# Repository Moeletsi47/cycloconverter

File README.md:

# Single-Phase Cycloconverter | ATmega328P

An embedded power-electronics project combining SCR switching, zero-crossing synchronisation, register-level C firmware, and a custom four-layer PCB designed in KiCad.

The intended input is **230 V AC RMS at 50 Hz**. The firmware runs an automatic sequence of frequency and voltage targets, then ramps down and disables gate firing.

## Operating sequence

The uploaded firmware uses a nominal **5 V/Hz** lookup table and the following sequence:

| Step | Frequency target | Nominal voltage target | Duration |
| --- | --- | --- | --- |
| Ramp up | 0 → 10 Hz | 0 → 50 V | 5 s |
| Hold | 10 Hz | 50 V | 2 s |
| Ramp up | 10 → 20 Hz | 50 → 100 V | 5 s |
| Hold | 20 Hz | 100 V | 2 s |
| Ramp up | 20 → 40 Hz | 100 → 200 V | 5 s |
| Hold | 40 Hz | 200 V | 2 s |
| Ramp down | 40 → 0 Hz | 200 → 0 V | 5 s |

After ramp-down, the controller remains in its stopped state until reset. The firmware reaches zero after 5 seconds of ramp-down and enters its final state at the next 500 ms update.

The hold-time comments in the source say 10 seconds, but the implemented thresholds are 2000 ms, giving **2-second holds**.

Voltage values are intended lookup-table targets, not measurements or closed-loop regulation. The switched output is non-sinusoidal; its RMS voltage and frequency spectrum require waveform verification, particularly at the 40 Hz setting.

## Firmware

The controller is an **ATmega328P running at 16 MHz**, programmed in embedded C using direct register access.

- **Zero-crossing interrupt:** PB0 / PCINT0 supplies the input timing reference.
- **Timer1:** Schedules the firing delay and gate-pulse duration with a prescaler of 64.
- **Gate pulses:** Approximately 300 µs, based on `PULSE_TICKS = 74`.
- **Timer2:** Generates a 1 ms timebase for the ramp and hold sequence.
- **Frequency control:** A phase accumulator selects the commanded output polarity at input half-cycle boundaries.
- **Voltage control:** `fire_table[]` selects a firing delay for each frequency setpoint.
- **Shutdown:** A zero-frequency setpoint prevents further gate firing.

The control sequence runs in interrupt service routines; the main loop remains idle.

## Pin mapping

| Signal | ATmega328P pin |
| --- | --- |
| Zero-crossing input | PB0 |
| T1 | PB1 |
| T2 | PB2 |
| T3 | PB3 |
| T4 | PB4 |
| N1 | PD4 |
| N2 | PD5 |
| N3 | PD6 |
| N4 | PD7 |

This firmware defines **eight gate outputs** in two groups. Confirm that the schematic and PCB revision match this mapping before using the firmware; the earlier four-SCR PCB arrangement must not be assumed to match it directly.

## Four-layer PCB design

The project also includes a **custom four-layer PCB designed in KiCad**, with attention to the separation of mains circuitry and low-voltage control electronics.

PCB design features include:

- Separate high-voltage power and low-voltage control regions.
- Isolation keepout regions around the optocoupler barrier.
- An internal ground pour confined to the low-voltage region.
- Wider copper tracks for the main SCR and load-current paths.
- Dedicated routing classes for power, mains sensing, and control signals.
- RC snubbers placed close to the associated switching devices.
- Input fuse and MOV provision.
- External power headers and terminal-block connections.

The design work covers schematic capture, footprint assignment, multilayer routing, and fabrication-output preparation. PCB layout completion does not by itself establish hardware validation or electrical-safety compliance.

## Development tools

| Tool | Purpose |
| --- | --- |
| Microchip Studio | AVR firmware development |
| Proteus | Circuit simulation and waveform inspection |
| KiCad | Schematic capture and four-layer PCB design |

## Current limitations and future improvements

- Output voltage is controlled through a fixed lookup table; the supplied firmware has no voltage-feedback loop.
- Input polarity is inferred by alternating a software flag at each accepted zero-crossing event.
- The supplied firmware has no current-zero detection or current-based interlock between converter groups.
- Planned improvements include current sensing, commutation interlocking, and measured calibration of the voltage targets.

## Safety

This project involves hazardous 230 V AC. Gate signals turning off do not force an SCR to stop conducting. Hardware testing requires appropriate protection, mains-rated measurement equipment, and verification of commutation behaviour, especially with inductive loads.

## Author

Jason Nkuna

Embedded systems, power electronics, and PCB design.

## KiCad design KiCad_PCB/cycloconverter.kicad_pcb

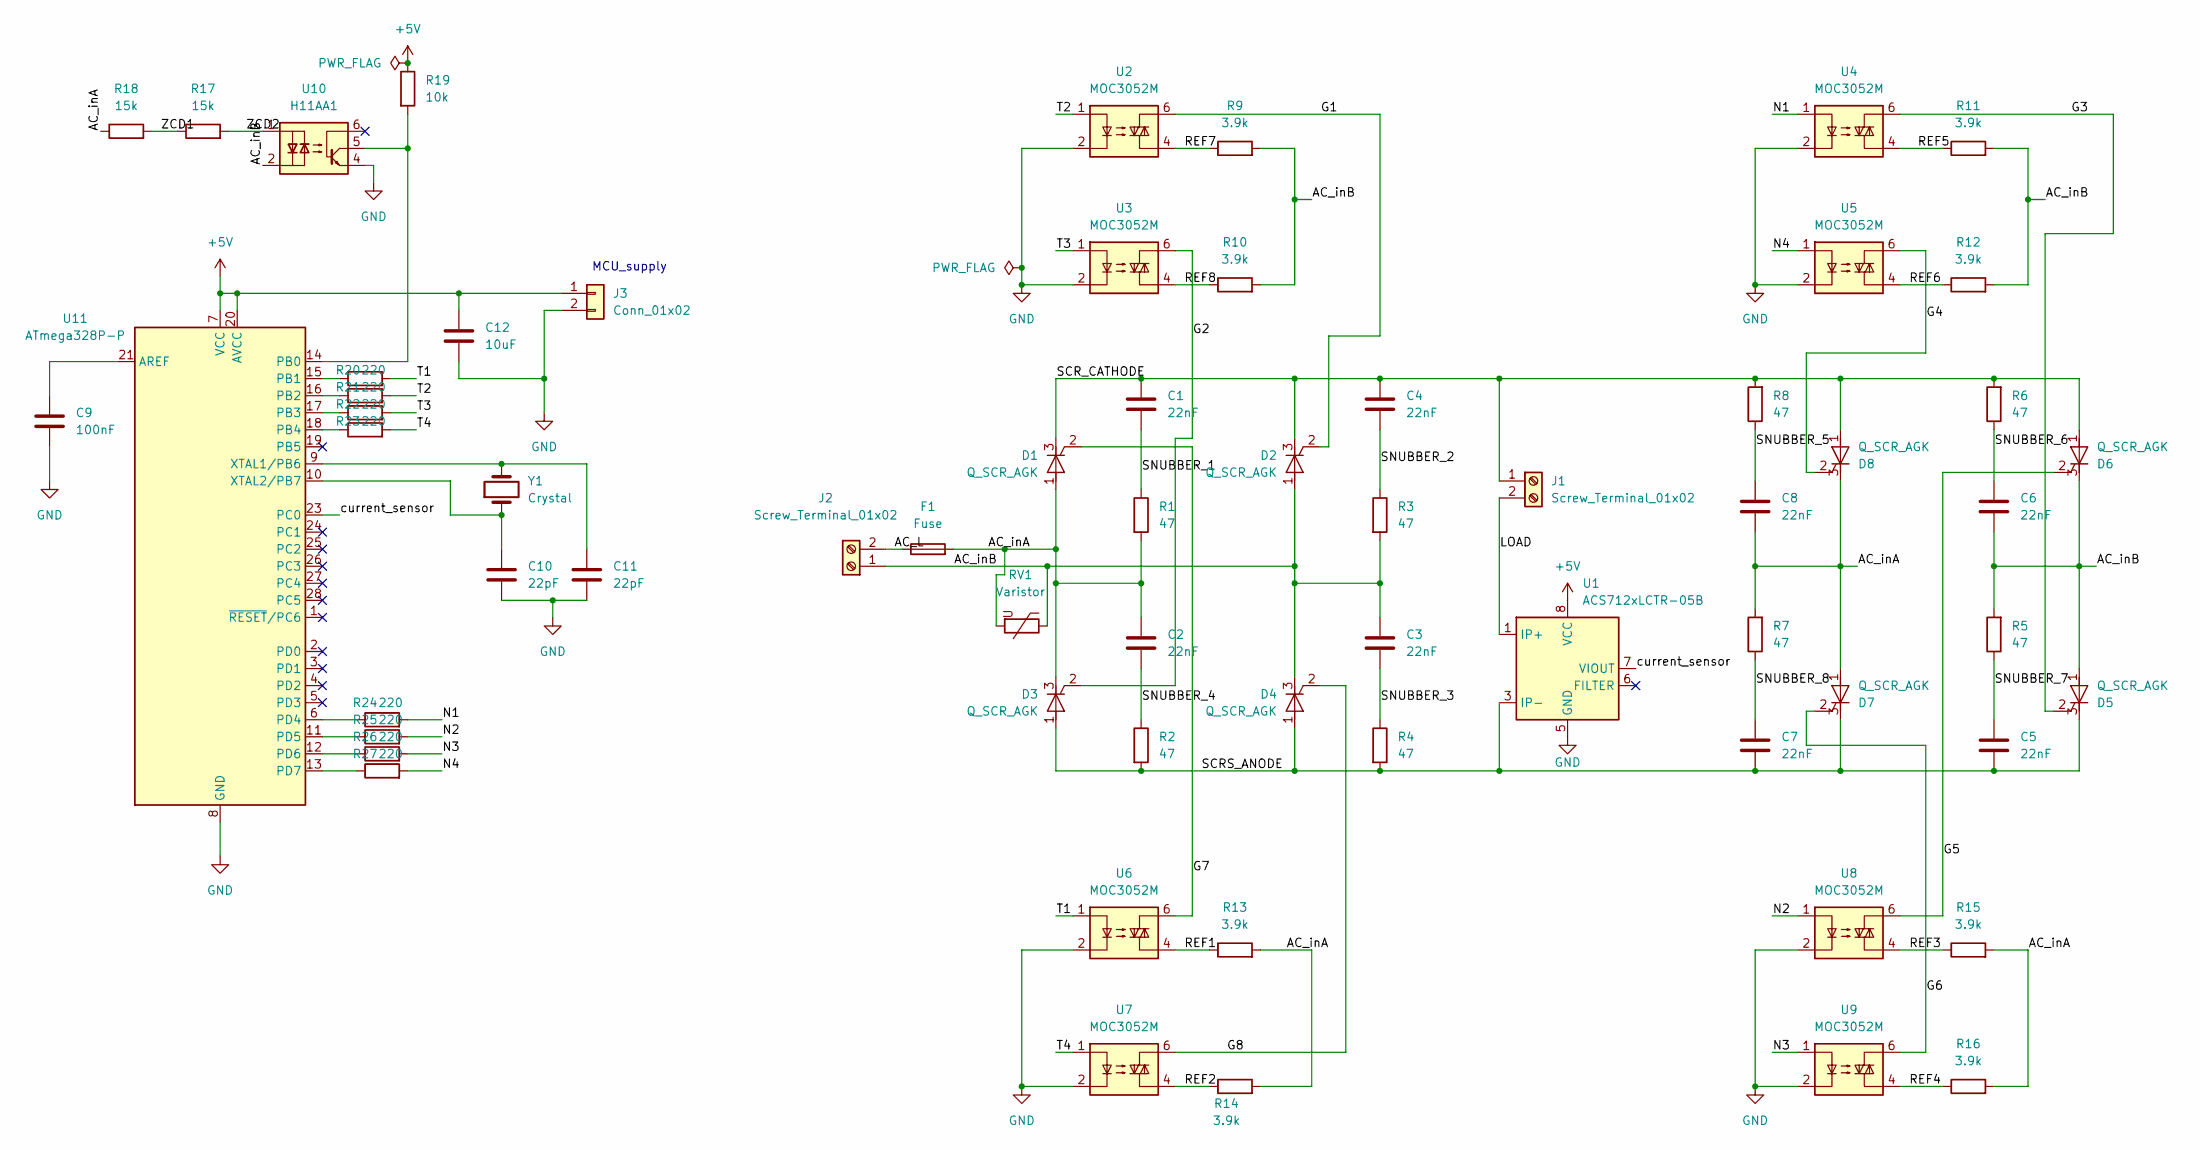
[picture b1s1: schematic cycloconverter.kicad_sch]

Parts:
C1, C2, C3, C4, C5, C6, C7, C8: 22nF; C_Rect_L18.0mm_W8.0mm_P15.00mm_FKS3_FKP3
C9: 100nF; C_Disc_D4.3mm_W1.9mm_P5.00mm
C10, C11: 22pF; C_Disc_D4.3mm_W1.9mm_P5.00mm
C12: 10uF; C_Disc_D4.3mm_W1.9mm_P5.00mm
D1, D2, D3, D4, D5, D6, D7, D8: Q_SCR_AGK; IFX-PG-TO220-3-904-1
F1: Fuse; Fuseholder_Clip-6.3x32mm_Littelfuse_102_Inline_P34.21x7.62m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
J1, J2: Screw_Terminal_01x02; TerminalBlock_Phoenix_MKDS-1,5-2_1x02_P5.00mm_Horizontal
J3: Conn_01x02; PinHeader_1x02_P2.54mm_Vertical
R1, R2, R3, R4, R5, R6, R7, R8: 47; R_Axial_DIN0516_L15.5mm_D5.0mm_P20.32mm_Horizontal
R9, R10, R11, R12, R13, R14, R15, R16: 3.9k; R_Axial_DIN0414_L11.9mm_D4.5mm_P20.32mm_Horizontal
R17, R18: 15k; R_Axial_DIN0411_L9.9mm_D3.6mm_P12.70mm_Horizontal
R19: 10k; R_Axial_DIN0207_L6.3mm_D2.5mm_P10.16mm_Horizontal
R20, R21, R22, R23, R24, R25, R26, R27: 220; R_Axial_DIN0207_L6.3mm_D2.5mm_P10.16mm_Horizontal
RV1: Varistor; RV_Disc_D15.5mm_W4.3mm_P7.5mm
U1: ACS712xLCTR-05B; SOIC-8_3.81x9.347mm_P2.54mm
U2, U3, U4, U5, U6, U7, U8, U9: MOC3052M; DIP762W46P254L851H508Q6
U10: H11AA1; DIP-6_W7.62mm
U11: ATmega328P-P; DIP-28_W7.62mm
Y1: Crystal; Crystal_HC49-U_Vertical

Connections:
+5V: C12.1, J3.1, R19.1, U1.8 (VCC), U11.7 (VCC), U11.20 (AVCC)
/AC_L: F1.1, J2.2
/AC_inA: C2.1, C8.1, D1.1 (A), D3.3 (K), D7.1 (A), D8.3 (K), F1.2, R1.2, R7.2, R13.2, R14.2, R15.2, R16.2, R18.1, RV1.2
/AC_inB: C3.1, C6.1, D2.1 (A), D4.3 (K), D5.1 (A), D6.3 (K), J2.1, R3.2, R5.2, R9.2, R10.2, R11.2, R12.2, RV1.1, U10.2
/G1: D2.2 (G), U2.6
/G2: D3.2 (G), U3.6
/G3: D5.2 (G), U4.6
/G4: D8.2 (G), U5.6
/G5: D6.2 (G), U8.6
/G6: D7.2 (G), U9.6
/G7: D1.2 (G), U6.6
/G8: D4.2 (G), U7.6
/LOAD: J1.2, U1.1 (IP+), U1.2 (IP+)
/N1: R24.2, U4.1
/N2: R25.2, U8.1
/N3: R26.2, U9.1
/N4: R27.2, U5.1
/REF1: R13.1, U6.4
/REF2: R14.1, U7.4
/REF3: R15.1, U8.4
/REF4: R16.1, U9.4
/REF5: R11.1, U4.4
/REF6: R12.1, U5.4
/REF7: R9.1, U2.4
/REF8: R10.1, U3.4
/SCRS_ANODE: C5.1, C7.1, D3.1 (A), D4.1 (A), D5.3 (K), D7.3 (K), R2.2, R4.2, U1.3 (IP-), U1.4 (IP-)
/SCR_CATHODE: C1.1, C4.1, D1.3 (K), D2.3 (K), D6.1 (A), D8.1 (A), J1.1, R6.2, R8.2
/SNUBBER_1: C1.2, R1.1
/SNUBBER_2: C4.2, R3.1
/SNUBBER_3: C3.2, R4.1
/SNUBBER_4: C2.2, R2.1
/SNUBBER_5: C8.2, R8.1
/SNUBBER_6: C6.2, R6.1
/SNUBBER_7: C5.2, R5.1
/SNUBBER_8: C7.2, R7.1
/T1: R20.2, U6.1
/T2: R21.2, U2.1
/T3: R22.2, U3.1
/T4: R23.2, U7.1
/ZCD1: R17.1, R18.2
/ZCD2: R17.2, U10.1
/current_sensor: U1.7 (VIOUT), U11.23 (PC0)
GND: C9.2, C10.2, C11.2, C12.2, J3.2, U1.5 (GND), U2.2, U3.2, U4.2, U5.2, U6.2, U7.2, U8.2, U9.2, U10.4, U11.8 (GND), U11.22 (GND)
unnamed: C9.1, U11.21 (AREF)
unnamed: R19.2, U10.5, U11.14 (PB0)
unnamed: R20.1, U11.15 (PB1)
unnamed: R21.1, U11.16 (PB2)
unnamed: R22.1, U11.17 (PB3)
unnamed: R23.1, U11.18 (PB4)
unnamed: R24.1, U11.6 (PD4)
unnamed: R25.1, U11.11 (PD5)
unnamed: R26.1, U11.12 (PD6)
unnamed: R27.1, U11.13 (PD7)
unnamed: C11.1, U11.9 (XTAL1/PB6), Y1.2
unnamed: C10.1, U11.10 (XTAL2/PB7), Y1.1

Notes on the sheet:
MCU_supply

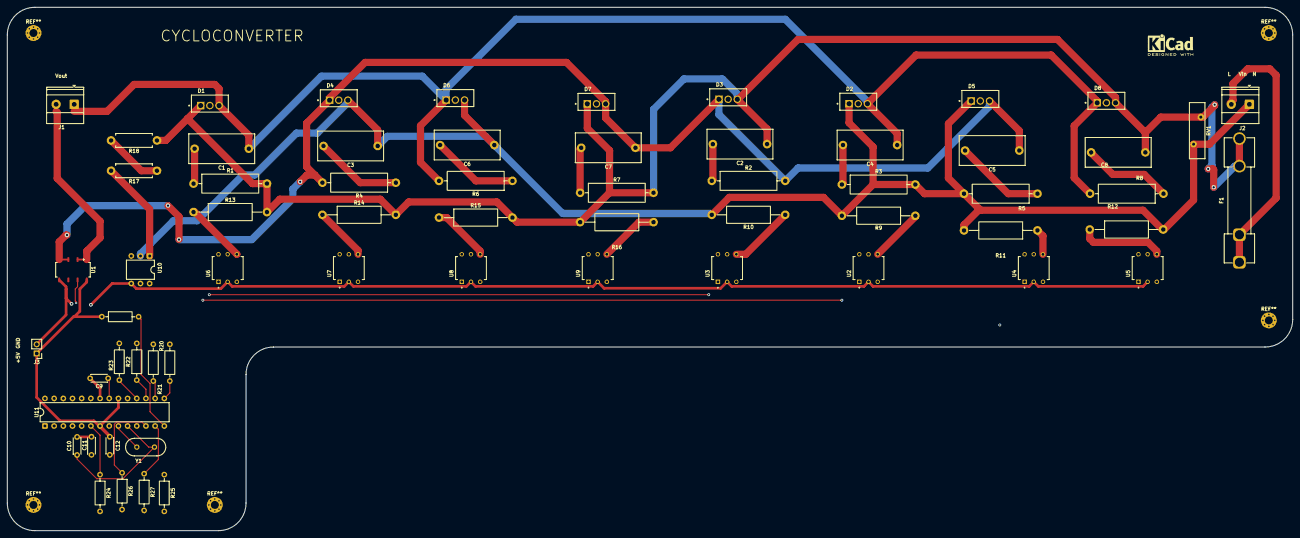
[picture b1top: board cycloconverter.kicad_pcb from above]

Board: 4 copper layers, 355.6 x 144.8 mm, 64 parts (0 on the bottom side), 55 nets.

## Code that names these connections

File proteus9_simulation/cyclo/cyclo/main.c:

#define F_CPU 16000000UL

#include <avr/io.h>
#include <avr/interrupt.h>
#include <stdint.h>

#define ZCD PB0

#define T1 PB1
#define T2 PB2
#define T3 PB3
#define T4 PB4

#define N1 PD4
#define N2 PD5
#define N3 PD6
#define N4 PD7

#define PULSE_TICKS 74

volatile uint8_t input_positive = 0;
volatile uint8_t output_positive = 1;
volatile uint8_t scheduled_input, scheduled_output;
volatile uint8_t timer_state = 0;

volatile uint8_t freq_hz = 0;
volatile uint8_t phase_acc = 0;
volatile uint16_t firing_ticks = 2499;

volatile uint16_t stage_ms = 0;
volatile uint8_t stage = 0;

/* V/f = 5 V/Hz */
const uint16_t fire_table[41] =
{
	2499,

	2396, 2335, 2283, 2236, 2193,
	2152, 2114, 2076, 2040, 2005,   // 10 Hz = 50 V

	1971, 1937, 1903, 1871, 1838,
	1806, 1774, 1742, 1710, 1678,   // 20 Hz = 100 V

	1645, 1613, 1581, 1548, 1515,
	1482, 1448, 1414, 1379, 1344,   // 30 Hz = 150 V

	1307, 1270, 1232, 1192, 1151,
	1108, 1063, 1015, 965, 910      // 40 Hz = 200 V
};

void gates_off(void)
{
	PORTB &= ~((1<<T1)|(1<<T2)|(1<<T3)|(1<<T4));
	PORTD &= ~((1<<N1)|(1<<N2)|(1<<N3)|(1<<N4));
}

void set_point(uint8_t f)
{
	freq_hz = f;

	if (f == 0)
	{
		firing_ticks = 2499;
		phase_acc = 0;
	}
	else
	{
		firing_ticks = fire_table[f];
	}
}

void fire_pair(void)
{
	gates_off();

	if (scheduled_output)
	{
		if (scheduled_input)
		PORTB |= (1<<T1) | (1<<T4);
		else
		PORTB |= (1<<T2) | (1<<T3);
	}
	else
	{
		if (scheduled_input)
		PORTD |= (1<<N2) | (1<<N3);
		else
		PORTD |= (1<<N1) | (1<<N4);
	}
}

void timer1_start(uint16_t x)
{
	TCCR1B = (1<<WGM12);
	TCNT1 = 0;
	OCR1A = x;
	TIFR1 = (1<<OCF1A);

	TCCR1B = (1<<WGM12)|(1<<CS11)|(1<<CS10);
}

void timer1_stop(void)
{
	TCCR1B = (1<<WGM12);
	TCNT1 = 0;
}

/* 1 ms timer */
ISR(TIMER2_COMPA_vect)
{
	stage_ms++;

	/* 0 -> 10 Hz in 5 s */
	if (stage == 0 && stage_ms >= 500)
	{
		stage_ms = 0;
		set_point(freq_hz + 1);

		if (freq_hz >= 10)
		stage = 1;
	}

	/* Hold 10 Hz / 50 V for 10 s */
	else if (stage == 1 && stage_ms >= 2000)
	{
		stage_ms = 0;
		stage = 2;
	}

	/* 10 -> 20 Hz in 5 s */
	else if (stage == 2 && stage_ms >= 500)
	{
		stage_ms = 0;
		set_point(freq_hz + 1);

		if (freq_hz >= 20)
		stage = 3;
	}

	/* Hold 20 Hz / 100 V for 10 s */
	else if (stage == 3 && stage_ms >= 2000)
	{
		stage_ms = 0;
		stage = 4;
	}

	/* 20 -> 40 Hz in 5 s */
	else if (stage == 4 && stage_ms >= 250)
	{
		stage_ms = 0;
		set_point(freq_hz + 1);

		if (freq_hz >= 40)
		stage = 5;
	}

	/* Hold 40 Hz / 200 V for 10 s */
	else if (stage == 5 && stage_ms >= 2000)
	{
		stage_ms = 0;
		stage = 6;
	}

	/* 40 -> 0 Hz in 5 s */
	else if (stage == 6 && stage_ms >= 500)
	{
		stage_ms = 0;

		if (freq_hz >= 4)
		set_point(freq_hz - 4);
		else
		{
			set_point(0);
			stage = 7;
		}
	}
}

ISR(PCINT0_vect)
{
	if (!(PINB & (1<<ZCD)))
	return;

	timer1_stop();
	gates_off();

	if (freq_hz == 0)
	{
		input_positive ^= 1;
		return;
	}

	scheduled_input = input_positive;
	scheduled_output = output_positive;

	timer_state = 1;
	timer1_start(firing_ticks);

	input_positive ^= 1;

	phase_acc += freq_hz;

	if (phase_acc >= 50)
	{
		phase_acc -= 50;
		output_positive ^= 1;
	}
}

ISR(TIMER1_COMPA_vect)
{
	if (timer_state == 1)
	{
		fire_pair();
		timer_state = 2;
		timer1_start(PULSE_TICKS);
	}
	else
	{
		gates_off();
		timer1_stop();
		timer_state = 0;
	}
}

int main(void)
{
	DDRB &= ~(1<<ZCD);

	DDRB |= (1<<T1)|(1<<T2)|(1<<T3)|(1<<T4);
	DDRD |= (1<<N1)|(1<<N2)|(1<<N3)|(1<<N4);

	gates_off();

	/* Timer1 - SCR firing */
	TCCR1A = 0;
	TCCR1B = (1<<WGM12);
	TIMSK1 = (1<<OCIE1A);

	/* Timer2 - 1 ms timebase */
	TCCR2A = (1<<WGM21);
	OCR2A = 249;
	TCCR2B = (1<<CS22);
	TIMSK2 = (1<<OCIE2A);

	PCICR |= (1<<PCIE0);
	PCMSK0 |= (1<<PCINT0);

	sei();

	while (1)
	{
	}
}
